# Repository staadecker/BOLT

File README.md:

# BOLT

BOLT is a machine that measures your reaction speed. The machine has 64 buttons which contain embedded LEDs. When an LED turns on, the user must press the matching button. The machine then calculates the user's reaction speed based on the time it took the user to press the button.

The project has two components.
- `arduino` : The arduino code that controls the buttons and LED's
- `bolt-mobile` : The Flutter code that uses a phone to communicate with the Arduino and displays the results\

This project reached a semi-functionning state but was not fully finished.

### Bluetooth

To communicate the Arduino and phone send each other packets over bluetooth. The packets' format is defined in `bluetooth-protocol.md`.

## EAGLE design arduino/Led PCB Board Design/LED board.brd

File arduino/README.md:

# Bolt Arduino

This folder contains the Arduino code for the BOLT project.

# Get started (with CLion)

1. Edit `CMakeLists.txt` to match your software setup.

2. Edit `lib/constants.h` to match your hardware setup.

3. Run the `upload-main` run configuration in CLion to upload the code.

4. Use the Serial Monitor plugin to monitor the Arduino serial.

# Implementation Details

## The Hardware Setup

The Arduino controls 64 buttons using a 64-button shield. It controls the LEDs using eight 8-bit shift registers. It communicates to a bluetooth device with an external bluetooth chip.

## The Code

The code that runs on the Arduino controls the LED's and registers the button presses. It also allows a device to connect via bluetooth. This device will be informed of button presses and will be able to send commands to turn the LEDs on or off.

### Arduino states (modes)

1. **Start state.** The board is either waiting for the user to switch to the offline state by pressing the middle button (#0) or the online state (switched to when a bluetooth packet is received).

2. **Offline state.** The state is a simple game that measures the users reaction speed.

3. **Online mode.** In this state, the arduino simply acts as a bridge between the buttons/LEDs and the phone. The Arduino is listening for bluetooth commands sent from the phone.

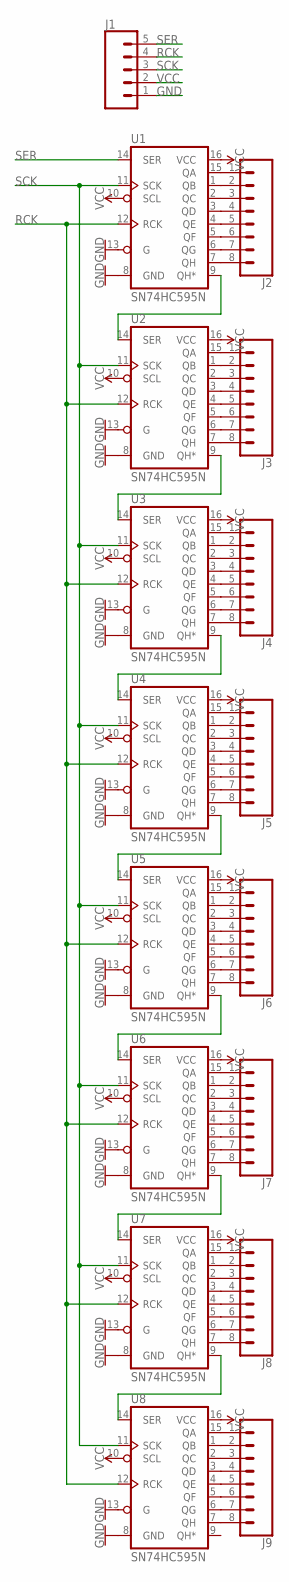
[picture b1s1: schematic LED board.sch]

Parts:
J1: CONN_05; 1X05
J2, J3, J4, J5, J6, J7, J8, J9: CONN_08"; 1X08
U1, U2, U3, U4, U5, U6, U7, U8: SN74HC595N; DIP16

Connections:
GND: J1.1, U1.8 (GND), U1.13 (G), U2.8 (GND), U2.13 (G), U3.8 (GND), U3.13 (G), U4.8 (GND), U4.13 (G), U5.8 (GND), U5.13 (G), U6.8 (GND), U6.13 (G), U7.8 (GND), U7.13 (G), U8.8 (GND), U8.13 (G)
unnamed: U1.9 (QH*), U2.14 (SER)
unnamed: U2.9 (QH*), U3.14 (SER)
unnamed: U3.9 (QH*), U4.14 (SER)
unnamed: U4.9 (QH*), U5.14 (SER)
unnamed: U5.9 (QH*), U6.14 (SER)
unnamed: U6.9 (QH*), U7.14 (SER)
unnamed: U7.9 (QH*), U8.14 (SER)
unnamed: J2.1, U1.15 (QA)
unnamed: J2.2, U1.1 (QB)
unnamed: J2.3, U1.2 (QC)
unnamed: J2.4, U1.3 (QD)
unnamed: J2.5, U1.4 (QE)
unnamed: J2.6, U1.5 (QF)
unnamed: J2.7, U1.6 (QG)
unnamed: J2.8, U1.7 (QH)
unnamed: J3.1, U2.15 (QA)
unnamed: J3.2, U2.1 (QB)
unnamed: J3.3, U2.2 (QC)
unnamed: J3.4, U2.3 (QD)
unnamed: J3.5, U2.4 (QE)
unnamed: J3.6, U2.5 (QF)
unnamed: J3.7, U2.6 (QG)
unnamed: J3.8, U2.7 (QH)
unnamed: J4.1, U3.15 (QA)
unnamed: J4.2, U3.1 (QB)
unnamed: J4.3, U3.2 (QC)
unnamed: J4.4, U3.3 (QD)
unnamed: J4.5, U3.4 (QE)
unnamed: J4.6, U3.5 (QF)
unnamed: J4.7, U3.6 (QG)
unnamed: J4.8, U3.7 (QH)
unnamed: J5.1, U4.15 (QA)
unnamed: J5.2, U4.1 (QB)
unnamed: J5.3, U4.2 (QC)
unnamed: J5.4, U4.3 (QD)
unnamed: J5.5, U4.4 (QE)
unnamed: J5.6, U4.5 (QF)
unnamed: J5.7, U4.6 (QG)
unnamed: J5.8, U4.7 (QH)
unnamed: J6.1, U5.15 (QA)
unnamed: J6.2, U5.1 (QB)
unnamed: J6.3, U5.2 (QC)
unnamed: J6.4, U5.3 (QD)
unnamed: J6.5, U5.4 (QE)
unnamed: J6.6, U5.5 (QF)
unnamed: J6.7, U5.6 (QG)
unnamed: J6.8, U5.7 (QH)
unnamed: J7.1, U6.15 (QA)
unnamed: J7.2, U6.1 (QB)
unnamed: J7.3, U6.2 (QC)
unnamed: J7.4, U6.3 (QD)
unnamed: J7.5, U6.4 (QE)
unnamed: J7.6, U6.5 (QF)
unnamed: J7.7, U6.6 (QG)
unnamed: J7.8, U6.7 (QH)
unnamed: J8.1, U7.15 (QA)
unnamed: J8.2, U7.1 (QB)
unnamed: J8.3, U7.2 (QC)
unnamed: J8.4, U7.3 (QD)
unnamed: J8.5, U7.4 (QE)
unnamed: J8.6, U7.5 (QF)
unnamed: J8.7, U7.6 (QG)
unnamed: J8.8, U7.7 (QH)
unnamed: J9.1, U8.15 (QA)
unnamed: J9.2, U8.1 (QB)
unnamed: J9.3, U8.2 (QC)
unnamed: J9.4, U8.3 (QD)
unnamed: J9.5, U8.4 (QE)
unnamed: J9.6, U8.5 (QF)
unnamed: J9.7, U8.6 (QG)
unnamed: J9.8, U8.7 (QH)
RCK: J1.4, U1.12 (RCK), U2.12 (RCK), U3.12 (RCK), U4.12 (RCK), U5.12 (RCK), U6.12 (RCK), U7.12 (RCK), U8.12 (RCK)
SCK: J1.3, U1.11 (SCK), U2.11 (SCK), U3.11 (SCK), U4.11 (SCK), U5.11 (SCK), U6.11 (SCK), U7.11 (SCK), U8.11 (SCK)
SER: J1.5, U1.14 (SER)
VCC: J1.2, U1.10 (SCL), U1.16 (VCC), U2.10 (SCL), U2.16 (VCC), U3.10 (SCL), U3.16 (VCC), U4.10 (SCL), U4.16 (VCC), U5.10 (SCL), U5.16 (VCC), U6.10 (SCL), U6.16 (VCC), U7.10 (SCL), U7.16 (VCC), U8.10 (SCL), U8.16 (VCC)

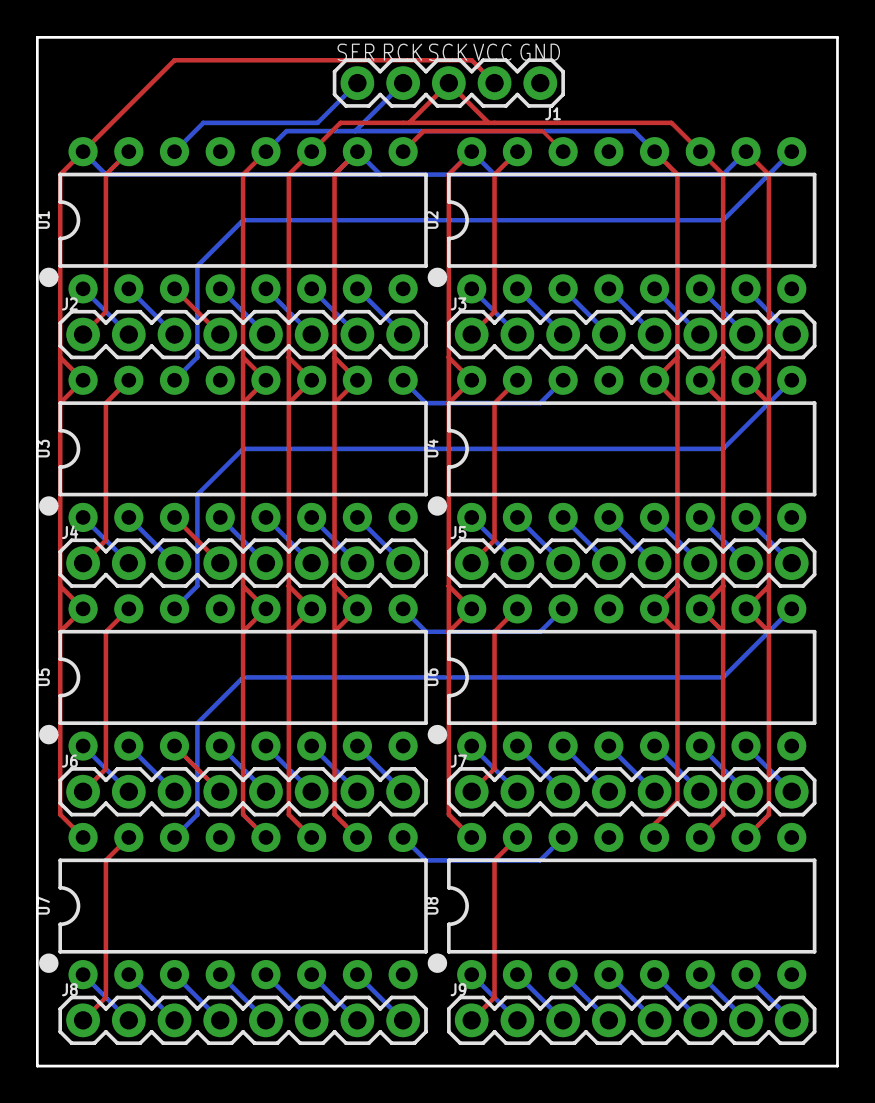
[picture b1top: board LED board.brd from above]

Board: 2 copper layers, 44.4 x 57.1 mm, 17 parts (0 on the bottom side), 76 nets.

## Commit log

2017-09-03 Framework for basic stand alone game. No hardware interaction except for buttons.
2017-09-03 Renamed main file to follow arduino project structure rules
2017-09-07 Added constants file and simplfied button.h
2017-09-07 Refatored clock thread. Updated to new naming convention
2017-09-07 Added thread controller
2017-09-07 Refactored game.h
2017-09-07 Added modes to clock thread
2017-09-08 Commented code. Minor refactor
2017-09-11 Add missing import to main .ino file
2017-09-11 Change default timer time to 0.
2017-09-11 Add button_isPressed in button.h for custom while loops
2017-09-11 Fix formatting
2017-09-13 Unfinished work on led class and shift out function
2017-09-13 Finish basic led.h class - no flashing
2017-09-13 Change button index system to start at 0
2017-09-13 Run auto format in arduino ide
2017-09-14 Change from byte to uint8_t
2017-09-14 Simplify ISR Method
2017-09-14 Support for flashing leds
2017-09-14 Refactor clock.h to use data stored in game.h
2017-09-16 Seperate into .cpp and .h files
2017-09-21 Add logger
2017-09-21 Add log statements
2017-09-25 Fix pointer issue with controller
2017-09-26 Fix bug in led shift out loop
2017-09-26 Fix header to be the same as cpp
2017-09-26 Add debug statements
2017-09-27 Most basic code
2017-09-27 Custom shift out method
2017-09-27 Low voltage shift out - working
2017-09-27 Working 5V led
2017-09-27 Working Low voltage shift out
2017-09-27 Working array for led states
2017-09-27 Working with 2 shift registors
2017-09-27 Working flasher, thread always running
2017-09-27 Working flasher, with thread disabled mode
2017-09-27 Seperate into different files
2017-09-27 Fixed logic for failing to add thread to control
2017-09-27 Added log statement
2017-09-27 Change flashing button to 0 from 1
2017-09-27 Add log statement
2017-09-27 Fix pin values
2017-09-27 Uncomment random function
2017-09-27 Move procedure to setup
2017-09-27 Turn of flashing light once game starts
2017-09-27 Add helper wait time method
2017-09-27 Add option for testing without button shield and screen
2017-09-27 Refactor NUMBER_OF_BITS and add log statements
2017-09-27 Make game repeat
2017-09-27 Remove dot from game end message and fix log statement
2017-10-11 Use namespaces
2017-10-11 Code refactor
2017-10-11 Major code changes and refactor
2017-10-11 Simplify function names (no longer avoid key names)
2017-10-12 Move main to setup to not repeat
2017-10-12 change pin const
2017-10-13 Add structure for offline and online mode
2017-10-13 Add shift out to set state
2017-10-13 Refactor flashing and led system
2017-10-13 Rework offline/online logic
2017-10-13 Simplify code for online mode
2017-10-14 Untested bluetooth code
2017-10-14 Reword bluetooth logic
2017-10-14 Rework bluetooth structure
2017-10-15 Better formatting when receiving unknown bytes
2017-10-15 Replace start time with end time
2017-10-15 Make button turn off after time ends
2017-10-15 Move constant from header to cpp
2017-10-15 Minor edits
2017-10-16 Rework bluetooth
2017-10-16 Remove controller
2017-10-16 Remove threads
2017-10-16 Add timeout for acknowledge
2017-10-16 Create NO_TIMEOUT constant
2017-10-16 Add clear button press method
2017-10-17 Remove format millis method
2017-10-17 Seperate shiftout from led on/off
2017-10-17 Update file to match protocol
2017-10-17 Minor bug fixes
2017-10-20 Fix bug where button is called twice - untested
2017-10-24 Fix bug with isr
2017-10-24 Change to average reaction speed
2017-11-07 Change print to write for bluetooth
2017-11-17 Working bluetooth
2018-07-25 Added SDK to Android module
2018-07-25 Ignored .idea folder
2018-07-25 Remove template README
2018-07-25 Remove .idea folder
2018-07-25 Now able to connect to device
2018-07-25 Setup read/write on bluetooth
2018-09-05 Fixed pins and sent AT command to receive connection changes
2018-09-05 Detect when connection is obtained or lost
2018-09-05 Auto detect connection on setup. Add comments. Simply code.
2018-09-05 Fixed bug with receiving packets due to no delay in loop
2018-09-05 Create basic working 2-way bluetooth communication with packets
2018-09-08 Working dialog with flutter connection
2018-09-08 Working count down triggered by button press
2018-09-10 Fixed bug with if statement. Enforced begin and end packets.
2018-12-25 Initial dummy commit
2018-12-25 Moved files to subdirectory
2018-12-25 Moved bolt-mobile files to subfolder
2018-12-25 Move bluetooth-protocol to parent directory
2018-12-30 Added led tester and refactored main code into sub-directory
2018-12-30 Merged tests and main into one sketch
2018-12-30 Added test for button press
2018-12-30 Remove indent for namespace
2018-12-30 Add test to test buttons with LEDs
2018-12-30 Add allLightsTest and made light turn off before 2 sec delay at end of game
2018-12-30 Add boot up sequence
2018-12-30 Simplify boot sequence
2018-12-30 Prepare for switch for bluetooth
2018-12-30 Add bluetooth-send-receive sketch
2018-12-30 Add PCB board design
2018-12-30 Fix README to match folder names
2019-01-16 Moved directories around
2019-01-16 Moved Arduino files around
2019-01-16 Create CMake
2019-01-18 Working CMake
2019-01-18 Fix project name
2019-01-18 Use new CMake file
2019-01-18 Fix CMakeLists
2019-01-19 Add windows support
2019-01-19 Update git ignore
2019-01-19 Remove constants namespace
2019-01-19 Use classes for buttons and games
2019-01-19 Use class for flash
2019-01-19 Move led and bluetooth to classes
2019-01-19 Clean code
2019-01-19 Made interface above button manager
2019-01-20 Working debug button press
2019-01-20 Not working code
2019-01-21 Changed to reference instead of copy and now it works.
2019-01-21 Fixed tests. Remove unnecessary arguments in Main,startReadyMode.
2019-01-22 Back up and working (somewhat)
2019-01-23 Fixed crashing issue (caused by global pointer pointing to local variable).
2019-01-24 Switch to threader model with working code
2019-01-25 Added comments and renamed variables for readability
2019-01-25 Rename ready mode to starting state
2019-01-25 Separated main and start state
2019-01-25 A bit of cleanup
2019-01-25 Fix issues with bluetooth and update protocol
2019-01-25 Update protocol to match changes
2019-01-25 Rename bolt-mobile folder to just mobile
2019-01-25 Fix tests
2019-01-28 Changed consts to #define and optimized
2019-01-31 Remove log statement
2019-01-31 Add comment for making wiring
2019-01-31 Update Flutter files
2019-02-04 Made one widget and renamed
2019-02-05 Removed outdated test
2019-02-07 Cleanup code and divide properly for bluetooth
2019-02-11 Cleanup and add comments to bluetoothConnector
2019-02-11 Update homescreen to a stateless widget
2019-05-04 Fixed bug where number of buttons pressed is not reset after an offline game
2019-05-04 Add details to README for setting up locally
2019-05-04 Fix bugs with delays caused by using ISR
2019-05-04 Make changes to button shield work for multiple button presses.
2019-05-05 Add comment and make method static in bluetooth manager
2019-06-19 Moved body to stateful widget so Navigator can be accessed.
2019-06-19 Fixed bug with Try Again button not capturing result
2019-06-20 Added debug statements and fixed problem with padding of zeros in button press packet
2019-06-21 Removed excess debug statements
2019-06-21 Add acknowledge when going online
2019-06-21 Fixed bug with not properly processing ON bluetooth commands
2019-06-22 Major refactor
2019-06-22 Remove screen.h
2019-06-22 Attempt to refactor more however disconnects
2019-06-22 Fix bug with disconnection and remove debug statements
2019-06-22 Fix bug with not properly reading number of button press
2019-06-23 Comment out acknowledge debug message
2019-06-24 Upgrade to AndroidX
2019-06-24 Upgrade to latest version of flutter blue
2019-06-24 Simplify syntax
2019-06-24 Refactor to latest version of flutter blue
2019-06-27 More work
2019-08-25 Refactor bluetooth connection
2019-08-25 Fixed tests
2019-08-25 Fix bug with writing packet failing

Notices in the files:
parts and their libraries:
SparkFun-Connectors: Licensing: Creative Commons ShareAlike 4.0 International - https://creativecommons.org/licenses/by-sa/4.0
